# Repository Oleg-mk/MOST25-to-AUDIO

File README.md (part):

# MOST25 to AUDIO

A passive listener for the MOST25 optical ring in a car. It sits in the
fibre as an invisible repeater - physically present, never a node: no
address, never a word on the control channel - and turns what the ring
carries into audio and data the owner can use:

- **J3: what the factory amplifier would play**, as stereo I2S and, the
  same stream, as S/PDIF on TOSLINK and coax: the main source with the head
  unit's volume, mute, balance, bass, treble and loudness applied, and up to
  three more of the amplifier's sinks - navigation and phone, the parking
  sensors, the chimes, where the car sends them as audio - mixed in at their
  own levels, so speakers moved to an
  amplifier or DSP of the owner's choice keep the car's controls and its
  voices;
- **J2: everything, raw**: every frame byte on two TDM8 lines, the control
  channel's blocks on UART, MCLK from the ring - for an analyser or a DSP.
  J2 and J3 show the frame as it leaves the listener: when the phone plays
  into the car's AUX channels, they carry the phone, as the factory
  amplifier after the listener does;
- **phone audio into the car**: a phone's Bluetooth stream while it plays,
  otherwise whatever plays into the board's TOSLINK input, replaces the bytes
  of the car's own AUX source while the amplifier plays them, so it is heard
  through the factory system with the factory controls.

**Status, 2026-10-12: designed and verified in simulation, host tests and
builds, but never built and never tried in a car.** Every file needed to
order, flash and assemble one is in this repository.

**This is a research project.** Every finding, recording, correction or bit
of help is welcome: open an issue or a pull request, or write in the forum
thread.

Its offspring, [JLR-MOST-Reader](https://github.com/Oleg-mk/JLR-MOST-Reader),
is the same receiver, DSP engine, S/PDIF coder and optical front end cut down
to one job on Jaguar and Land Rover: the amplifier's stereo out on TOSLINK.

Ukrainian: [README.uk.md](README.uk.md).

## Which cars

- **What the car must have:** a MOST25 ring that carries the entertainment
  audio to a separate amplifier as plain PCM. Cars without that external
  amplifier keep the audio inside the head unit, and the ring carries little
  or none of it; a copy-protected stream (DTCP) gives nothing to play either.
  Having MOST25 does not make a car one of them - only a recording of that
  car says.
- **Both ring rates:** 48 kHz (Jaguar and Land Rover) and 44.1 kHz (Audi MMI
  2G/3G/3G+, BMW E65/F01). The receiver learns the bit time from the line, and
  the regenerator's clock is centred on the measured rate.
- **The controls:** every source agrees that the PCM on the ring is the same at
  any volume, and that the amplifier applies the volume, balance, tone and
  mixer levels. So the listener reads the control channel and applies them
  itself. Known: Jaguar and Land Rover (the gateway's 0xF0.0x409 levels and the
  amplifier's 0x22.0x46D SpeakerLevel) and BMW (AudioMaster 0x20.0x200);
  Mercedes, VAG and Volvo are not public. Every scale is a placeholder until
  that car's ring is recorded, and the listener's own console trace is the
  tool for it (`listener_fw/README.md`, Recording). Until it has heard one of
  the volume messages it knows, J3 stays silent (the chimes excepted).
- **The phone into the car** needs the car's AUX to be a MOST source: where AUX
  is mixed inside the head unit there are no AUX bytes to replace. It also needs
  the listener on the fibre into the amplifier: the phone goes into the frames
  as they leave the listener, so only the nodes after it hear it. For listening,
  any place in the ring will do.

[docs/vehicle_survey.md](docs/vehicle_survey.md) lists each car with its
sources and how sure each fact is.

## Is it safe for the car's ring?

- **The ring's path:** the fibre receiver, a buffer, a multiplexer (U2) and the
  fibre transmitter. U2 passes either the fibre's own signal or the FPGA's
  regenerated one. That path runs on the always-on 3.3 V (3V3_AON, U5), fed
  from KL30 and drawing tens of microamps with the car parked.
- **The bypass:** U2 falls back to the fibre's own signal whenever the FPGA is
  off or not configured, has not locked to the ring, or its transmit edges
  stop; a watchdog (U11) does that last even if the FPGA's clocks die. So a
  failure of the FPGA, its clocks or the regeneration leaves the ring passing
  straight through.
- **The switch:** when the listener locks and moves the ring from the plain
  path to its regenerated one, the ring sees a short phase step, as it does when
  any MOST node leaves its bypass at start-up. The next node relocks within a few
  frames, and the amplifier may mute for that moment.
- **When the ring opens:** the bypass is an electrical path, not an optical
  one. If its supply is lost (a blown fuse, KL30 disconnected) or a fibre part
  fails, the ring opens, as with every factory MOST node. Fit your own fuse
  where you tap KL30.
- **Nothing new on the network:** no address, never a word on the control
  channel. Until injection is allowed, the frames leave as they came.
- **Injection is off until you allow it** ('i' on the host's console, kept in
  flash; a new module has it off). Then it replaces only the bytes of the car's
  own AUX source while the amplifier plays them, and the FPGA drops it 2 s after
  the host's last command, so a host that hangs takes the phone out.
- **Fully reversible:** unplug the loop-in cable and the car is back to stock.

## Status: what is proved and what is not

**Verified in models** (run `python check_all.py`; every step passes, and
`--sweep` adds 32 random rings):

- The gateware, in Icarus Verilog against Python models:
  - the receiver, and the J3 engine at 48 and 44.1 kHz, word for word against
    its model;
  - the S/PDIF output, decoded back;
  - the whole core from the optical line, in 14 corners: both rates, preamble
    variants, injection, gaps in the control blocks, a dead transmit feedback, a
    stopped clock, bit errors, the Si514's start and its loss, the capture,
    fades, the injection's lease, and a deliberate fault the checks must catch;
  - the regenerator's clock loop, and 32 random rings.
- The host's firmware: its tests on the PC and the ESP-IDF build with no
  warnings. JLR-MOST-Reader's checks compile its decoder and gain tables and
  compare them with their own.
- The Gowin build meets timing with at least 10 % margin; the bitstream and
  the firmware in `kit/2_flash` were built from the committed sources.
- The boards: ERC and DRC clean, with parity between sheet and board, for v1.6
  and v2.0; v2.0's sheet held to v1.6's part for part and net for net; the
  board's fit in the tube and its caps from one model; the fab packages and
  the kit reproduced from the commit.
- The laptop's recorder and decoder, against the host's own formats.

**Unknown until a bench or a car:**

- **The line:** the preamble's full pattern, which variant marks a block start,
  the parity rule. The simulations assume them; the capture (command 04)
  settles them on the first ring.
- **The per-car scales:** volume, tone and the mixer levels stay placeholders
  until a recording of the car's controls.
- **The car's own messages:** whether a stock head unit sends 0x22.0x111
  Connect at all (J3 and the phone into the car take their channels from it);
  which of 0xF0.0x409 and SpeakerLevel a Jaguar XF's amplifier gets, and
  0x409's byte positions (two layouts in one author's code, the later one
  used); whether JLR mutes with 0x113 or with 0x466 MuteParameters; whether
  the parking sensors and the chimes travel the ring as audio, as mObridge's
  guide says for JLR. The capture and the recording settle these too.
- **Real hardware:** no board has been powered, the regeneration has never run
  in a real ring, and no real S/PDIF receiver has taken the output.

Bring-up goes in three steps, each with a recording (Bring-up, in this order,
below).

## Build one

The full guide is [BUILD.md](BUILD.md); `kit/` holds the same in Ukrainian with
every file to order, flash and fit. There are two boards with the same
circuit. **v2.0** (`listener_hw2/`) is the one to build: 98 x 60 mm, four
layers, inside an 80 x 30 x 2 mm aluminium tube with two 3D-printed end caps.
v1.6 (`listener_hw/`) is the first, flat board, 123.55 x 78.9 mm on two layers.

1. **Order the boards** from JLCPCB, with the SMD parts assembled on both
   sides. Everything is in `listener_hw2/fab/`, copied into `kit/1_boards/`.
   One board gives three assemblies:

   | Assembly | What works | Parts JLCPCB places |
   |---|---|---|
   | min | the core and the S/PDIF outputs: J6 (TOSLINK) and J7 (coax) | 103 |
   | mid | min and the line out, J8 and J9 | 143 |
   | max | mid and the TOSLINK input, J5 | 163 |

   U7, the Si514, is not in JLCPCB's stock: send your own, or have JLCPCB pre-order it.
   Any 3.3 V CMOS variant in the 3.2 x 5 or 2.5 x 3.2 package fits, for example
   514CBB000112BAG, which DigiKey sells singly and JLCPCB can pre-order (C1670489).
2. **Buy the hand-soldered parts:** J1 (TE 1-1394640-1, the MOST FOT header:
   marketplaces only, look early), J4 (Molex 43650-0200), J5 and J6 (Cliff
   FCR684208R and FCR684208T), J7..J9 (BKL Electronic 0101153), J2 and J3 (pin
   headers), M1 (Sipeed Tang Nano 20K), M2 (Espressif ESP32-DevKitC-VIE) and the
   modules' pin headers.
3. **The enclosure:** the tube, cut to the soldered board's length; the two
   caps, printed from `listener_hw2/caps/` in PETG or ASA; a 150 mm U.FL-to-SMA
   pigtail and a 2.4 GHz antenna; screws.
4. **Flash both modules before soldering them** (`kit/2_flash/`): once M1 is in,
   the RCA jacks cover its USB-C.
5. **Assemble, power up on the bench, then fit the tube**, as BUILD.md says.
6. **In the car**, one step at a time, each with a recording (`kit/3_laptop/`):
   the bypass and listening first, then the regeneration, then the injection.

Also needed: a 12 V feed from KL30 with a fuse of your own, and a loop-in cable
that opens the ring at one node and brings it to J1 (Kufatec, Dension and
Trioma make them).

## Rough cost

| Item | Approx. USD | Basis (seen 2026-10-12) |
|---|---|---|
| JLCPCB: 5 boards, 2 of them assembled on both sides | min 200-230, mid 225-255, max 275-310, plus shipping and tax | JLCPCB's quote and assembly price page: 5 bare boards (4 layers, ENIG) $25; SMD on both sides needs Standard PCBA, $51 setup and $16 stencil for both sides plus $1.53 per part line; the parts for two boards $25 (min) to $75 (max), most of max's being U13 (SRC4192, about $17.56); two Si514s pre-ordered, $17-24 |
| Sipeed Tang Nano 20K | 26-32 | $25 at launch; Spotpear $31.90 |
| Espressif ESP32-DevKitC-VIE | 11-14 | DigiKey $11.00 |
| TE 1-1394640-1 (J1) | 22-27, plus shipping | no distributor stocks it; eBay about $22 (2026-10-12), AliExpress about $27 (2026-10-13) |
| Cliff FCR684208R and FCR684208T (J5, J6) | 13 | DigiKey $7.83 + $5.22 |
| 3 x BKL Electronic 0101153 (J7..J9) | 28-33 | Bürklin, €8.35-9.94 each |
| J4 with its plug, the pin headers, a fuse and wire for the 12 V tap | 5-10 | DigiKey; the fuse and wire rough |
| The tube, the printed caps, screws | 3-12 | the tube about 335 UAH a metre; 23 g of PETG |
| U.FL-to-SMA pigtail and a 2.4 GHz antenna | 4-11 | Adafruit 851 $3.95; a TE Linx antenna $7.13 |
| MOST loop-in adapter, TOSLINK cable | 25-50, plus shipping | a MOST25 splitter on Tindie $20, a Dension set about €40, depending on the node you tap; TOSLINK $5-7 |

The first listener comes to roughly $340-435 for min, $365-460 for mid and $415-515 for max,
plus shipping and tax. The second board from the same order is already assembled and paid for:
its modules, hand parts, enclosure and cables add about $140-205. Most of the order is JLCPCB's
fixed fees for assembling both sides, so more boards from one order cost less each.

## Repository map

| Folder | What | Built with |
|---|---|---|
| [listener_hw2](listener_hw2) | **board v2.0, the one to order**: v1.6's circuit on 98 x 60 mm and four layers, for an aluminium tube 80 x 30 x 2 mm; the sheet written by `gen_listener2.py` from v1.6's generator and held to v1.6 by `tools/check_v2_circuit.py`; the manufacturing package for three assemblies in `fab/`, written by `make_fab2.py`; the board in the tube modelled by `check_fit.py`, the two printed end caps in `caps/`, written by `gen_caps.py`; the pictures in `views/`, rendered by `make_views.py` - see The board, v2.0 | Python, KiCad 10 |
| [listener_hw](listener_hw) | board v1.6, the first one, and the circuit's source: one KiCad 10 sheet, generated by `gen_listener.py` (symbols and the footprints drawn from the makers' drawings included: Si514, the TOSLINK housings, the RCA jack, both modules; the bodies of the FOT, the TOSLINK housings and the RCA jack for the 3D view too); the manufacturing package in `fab/`, written by `make_fab.py`: Gerbers and drill files, BOM, pick-and-place, and JLCPCB's BOM and CPL for an order with the SMD parts assembled; TOSLINK in through DIR9001 and SRC4192, S/PDIF out on TOSLINK and coax; J3's stereo as an analog line out on two RCA through a PCM5102A and an OPA1678 buffer with a 60 kHz low-pass; test points for the bench. The PCB, 123.55 x 78.9 mm on two layers, first laid out by `gen_listener_pcb.py` from the same sheet (every part's place and why is in that file), placed by hand in KiCad and routed over a ground plane - see Board v1.6 | Python, KiCad 10 |
| [listener_gw](listener_gw) | FPGA (Sipeed Tang Nano 20K): receiver, regenerator on a ring-locked clock (an Si514 the FPGA steers), TDM/UART outputs, J3's DSP engine and its S/PDIF twin, audio injection from the host or the S/PDIF input | Gowin EDA 1.9.12; simulation: Icarus Verilog (OSS CAD Suite) |
| [listener_fw](listener_fw) | ESP32 host (M2, ESP32-DevKitC-VIE): Bluetooth A2DP in (AAC, SBC), the phone's rate onto the ring's, MOST telegram decoding, the amplifier model, J3's coefficients, the steering wheel's track keys to the phone (AVRCP) | ESP-IDF v6.1; host tests: gcc |
| [virtual_most_source](virtual_most_source) | MOST25 frames and Biphase Mark line coding - the simulations' stimulus | Python + numpy |
| [tools](tools) | `console_log.py`: a recording of the host's console on a laptop on M2's USB port, kept whole, with marks and alarms (the port lost, the ESP32 started anew, a loss counter rising, silence); `trace_decode.py`: that recording at home - every telegram, the sound values a car's scales are fixed from, the telegrams beside each mark, the starts, losses and silences, and each dump through `capture_analyse.py`: what a recording of a real line says (UI and rate, preamble patterns, block marker, parity rule, frame control); each with its test (the console's formats against host.c's own, a made-up recording, known frames) | Python; pyserial for the recorder |
| [kit](kit) | what the project hands over, without the rest of the repository: `1_boards` v2.0's order (JLCPCB's files for the three assemblies, the BOM, the schematic and assembly PDFs, the parts by hand, the tube's printed caps, the first power-up, the assembly into the tube), `2_flash` the FPGA's bitstream and the host's firmware with how to write each from Windows or macOS, `3_laptop` the recorder and the decoder with their launchers; written by `tools/make_kit.py`, the builds only from committed sources, checked by `check_all.py` | Ukrainian READMEs; the same in English is [BUILD.md](BUILD.md) |
| [BUILD.md](BUILD.md) | the build guide in English: the order, the parts, flashing, the assembly, the tube, the first power-up, the laptop's recorder | - |
| [SOURCES.md](SOURCES.md) | where the knowledge of MOST25, of the cars' messages and of the parts comes from | - |
| [docs](docs) | the MOST control formats the host decodes, which cars carry audio and how they send volume, the research behind the regenerator's clock | - |

Each part's README says how it works, what is verified and how.

## Build and test

```text
python check_all.py            everything, one step at a time (~40 min)
python check_all.py --quick    without the clock loop's long runs
python check_all.py --sweep    plus the whole core over 32 random rings (~1 h more)
```

It runs the steps strictly one after another and stops at nothing: each
prints PASS or FAIL, and the summary lists them. The simulation scripts
themselves run one simulation at a time too. Tools it expects (override with
environment variables, see the script's header):
OSS CAD Suite in `~/toolchains/oss-cad-suite`, Gowin EDA in
`C:\Gowin\Gowin_V1.9.12.03_x64`, ESP-IDF v6.1 in `~/toolchains/esp-idf`
(tools in `~/toolchains/espressif`), MinGW gcc in `~/toolchains/mingw64`,
KiCad 10.

## The board, v2.0

v2.0 (`listener_hw2/`; `most_listener_v2.kicad_pro` opens it in KiCad 10) is the board to order:
v1.6's circuit on a board of 98 x 60 mm with four layers, made to slide into an aluminium tube
80 x 30 x 2 mm closed by two printed caps. The inputs sit at one end - J1 (the ring's FOT), J5
(TOSLINK in), J4 (power) - and the outputs at the other - J6 (TOSLINK out), J7 (coax S/PDIF), J8
and J9 (the line out). M1 (the FPGA) stands on top; M2 (the host) hangs underneath, component side
down, its micro-USB at the input end. In1 and In2 are solid ground under both signal layers.

- **The sheet** is not drawn twice. `gen_listener2.py` loads v1.6's `gen_listener.py` and writes its
  blocks with v2.0's title and UUIDs, J5 and J6 as Cliff ORJ-8/OTJ-8 (10 mm high, no screw ear), the
  modules' footprints with holes only for the pins in use and the corner pins, and the parts
  v2.0 adds: R47 10R + C84 10u and R48 10R + C85 10u filter the line out's rails,
  R49..R51 (33R) sit in I2S's BCLK, LRCK and DOUT, R52 (33R) in RX_IN at U3, R53 (33R) at U1's
  output. `tools/check_v2_circuit.py` holds the sheet to v1.6's part for part and net for net, these
  parts taken out, so the gateware, the firmware and `kit/2_flash` hold for both boards.
- **The PCB** was placed once by `gen_listener2_pcb.py` and routed, then edited round by round in
  the PCB editor; the ring's FOT block is the reader v2.0's (JLR-MOST-Reader). It passes DRC with no
  error, nothing unconnected and no difference from the sheet.
- **Three assemblies, one board and one case.** Every connector is fitted in each; they differ in
  the parts behind the connectors: min (the core and the S/PDIF outputs), mid (+ the line out), max
  (+ the TOSLINK input). `make_fab2.py` writes `fab/` from the board and the sheet: the Gerbers and
  drill files, the BOM, the pick-and-place of both sides, JLCPCB's BOM and CPL for each assembly,
  the schematic and the assembly drawings of both sides, and a README with the order's steps.
- **The tube.** `check_fit.py` models the board in the tube from the PCB and every part's height,
  each with its source: the board centred across, 8 mm a side, at the height that leaves the same
  room over the tallest parts on top (the RCA jacks) and under M2; each part's face against its cap;
  the leads under the board; the caps' openings and the webs between them. `gen_caps.py` writes the
  caps into `caps/` (STEP, STL, a drawing, a README), and writes nothing when a wall comes out
  thinner than a printer makes or a block meets a part or a lead. Each cap is a flange on the tube's
  end, blocks in the side margins that hold the board's edges in slots, 0.7 mm off the tube's walls
  so any tube in tolerance takes them, and a saddle under the tube with an ear either side to screw
  it down. The input cap passes J1, J5 with J4, M2's micro-USB and the Bluetooth antenna's SMA jack;
  the output cap J6 and the RCA jacks.
- **What the tube asks.** M1's USB-C ends up behind the RCA housings, so the FPGA is flashed before
  M1 is soldered in and cannot be flashed in the assembled board; the host's micro-USB stays
  reachable through the input cap, for its firmware and for the laptop's recording. J2 and J3 are
  for the bench: a crimp housing on them would stand 16.4 mm high, and the tube leaves 14.75.
- **The pictures** here are rendered by `make_views.py` from the same models. KiCad has no body for
  the modules and four of the parts, and plain boxes stand in for them.

`check_all.py` regenerates v2.0's sheet and holds it to v1.6's, runs ERC and DRC, runs
`check_fit.py` and `gen_caps.py`, and fails while `fab/` or `caps/` differ from what their scripts
write. `kit/1_boards` hands v2.0 over: the order of each assembly, the parts by hand, the tube and
its caps, the assembly into the tube.

## Board v1.6

Board v1.6 is the first board, on two layers; its sheet is v2.0's circuit too.
`listener_hw/most_listener.kicad_pro` opens the project in KiCad 10. The sheet
is generated (`gen_listener.py`); the PCB was laid out once by
`gen_listener_pcb.py`, then placed by hand in the PCB editor and routed. From there on
`most_listener.kicad_pcb` is the master: parts may be moved freely, and the
generator refuses to overwrite the file unless run with `--fresh`, which lays
the parts out again from its table and discards every track.

What the board already carries: the outline (123.55 x 78.9 mm, two layers), four
M3 holes about 4 mm from their edges, ground pours on both sides (B fills them), the copper keep-out
under M2's antenna, the net classes - Default 0.25 mm tracks with 0.15 mm
clearance, Rail 0.35 mm for the 3.3 V rails, Power 0.6 mm for the battery path
and the 5 V rails, vias 0.6/0.3 and 0.8/0.4 mm - and `most_listener.kicad_dru`,
which lets one resolved thermal spoke connect a pad to a pour. The reasons
behind every part's place are in the generator's table.

The routing (board v1.6): the bottom is one ground plane, crossed only by
short jumpers (4 of them, 9 mm in all, the longest 3.65 mm); signals and
supplies run on top, the supplies as wide tracks that change layer nowhere but
at one 3V3_AON jumper, and the top's ground pour is stitched to the plane by
vias about every 6 mm. Every SMD ground pad has a via of its own beside it. The
5 V trunk runs 1 mm wide from C7 up the left edge under J1 and along the top
edge; the host's switch U10 sits at M2's 5 V pin with 10 uF at its input (the
radio's pulses come out of it, not over the trunk); 100 uF + 100 nF (C63, C64)
sit by D3 at the module's end of the trunk, 100 uF + 100 nF (C81, C80) at its
other end by U10 and U14, four more 100 nF (C65-C68) along it.
M1 and M2 are soldered to the board on pin headers, no sockets - two 1x20 and
two 1x19 on 2.54 mm, which the 3D view shows under them, as it shows J2's and
J3's. The headers' plastic leaves 2.5 mm under each module: room for the 0603
resistors under M1 (R11, R12) and under M2 (R18..R21, R34..R41);
M2's courtyard is its two pin rows and the antenna's end.
KiCad has no model for the MOST FOT, the TOSLINK housings or the RCA jacks, so
`gen_listener.py` draws their bodies from the same drawings, as STEP files in
`most_listener.3dshapes`.
`make_fab.py` writes the manufacturing package into `listener_hw/fab`: the
Gerbers and drill files (zipped for the board house), the BOM, the pick-and-place
file, the same two in JLCPCB's format, and a README with the board's numbers and
the notes the BOM's values do not carry. JLCPCB's rotations were read off each
chosen part's LCSC footprint.
`check_all.py` fails while the package does not match the board.

Every footprint is linked to its symbol, so after a change of the sheet: run
`gen_listener.py`, then in the PCB editor Tools > Update PCB from Schematic. `python check_all.py` runs KiCad's DRC on
the board as it is, checked against the sheet; the board passes with no error
and nothing unconnected. Warnings are silk only: references the hand placement
left overlapping a pad or another reference.

## Limits, by design

- **Only the light tells the host what plays.** The listener never sends a
  word, so the host learns which frame bytes carry the AUX source, and whether
  the amplifier plays them, only from the telegrams it happens to hear. At a
  cold start the ring, the FPGA and the ESP32 wake together (WAKE); if the
  head unit connects the amplifier to AUX before the host is listening, the
  phone is not injected until the head unit next changes a source. The FPGA
  reads its bitstream from the module's flash in about 290 ms, so that window
  is kept short. Asking (a SourceInfo.Get on the control channel) would end
  the listener's silence, so this stays as it is.
- **Cars whose AUX is not a MOST source** - mixed inside the head unit - have
  no AUX bytes to replace; the phone cannot be injected there. Listening
  (J2, J3) needs the audio on the fibre as plain PCM: cars without the
  external amplifier, or with a copy-protected stream (DTCP), give it nothing
  to play (docs/vehicle_survey.md). Having MOST25 does not make a car one of
  them - only a recording of that car says.
- **The per-car scales** - volume, tone, the Jaguar XF's navigation and
  parking-sensor levels (0xF0.0x409 bytes 9 and 11) - are placeholders until
  a real ring is recorded.
- **Sink 4 is the chimes in every car**, as Jaguar Land Rover numbers the
  amplifier's sinks: with no SpeakerLevel of its own it plays at -6 dB,
  never at the volume, so a chime is heard with the volume down. A car
  that puts something else on sink 4 gets that at -6 dB too.
- **What an amplifier does on its own** is not on the bus: if it turns the
  music down while a prompt plays, J3 does not; it follows what the head unit
  sends (levels, mutes).
- **The control channel's CRC is not checked**: its polynomial is in no
  document we have. What is checked instead: the FPGA drops a block in which
  the line broke its code, and the host drops a block whose frames disagree
  in parity (the count a clean block has is learnt on the ring). A bit can
  still flip unseen in a way neither shows; the CRC follows once a recording
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
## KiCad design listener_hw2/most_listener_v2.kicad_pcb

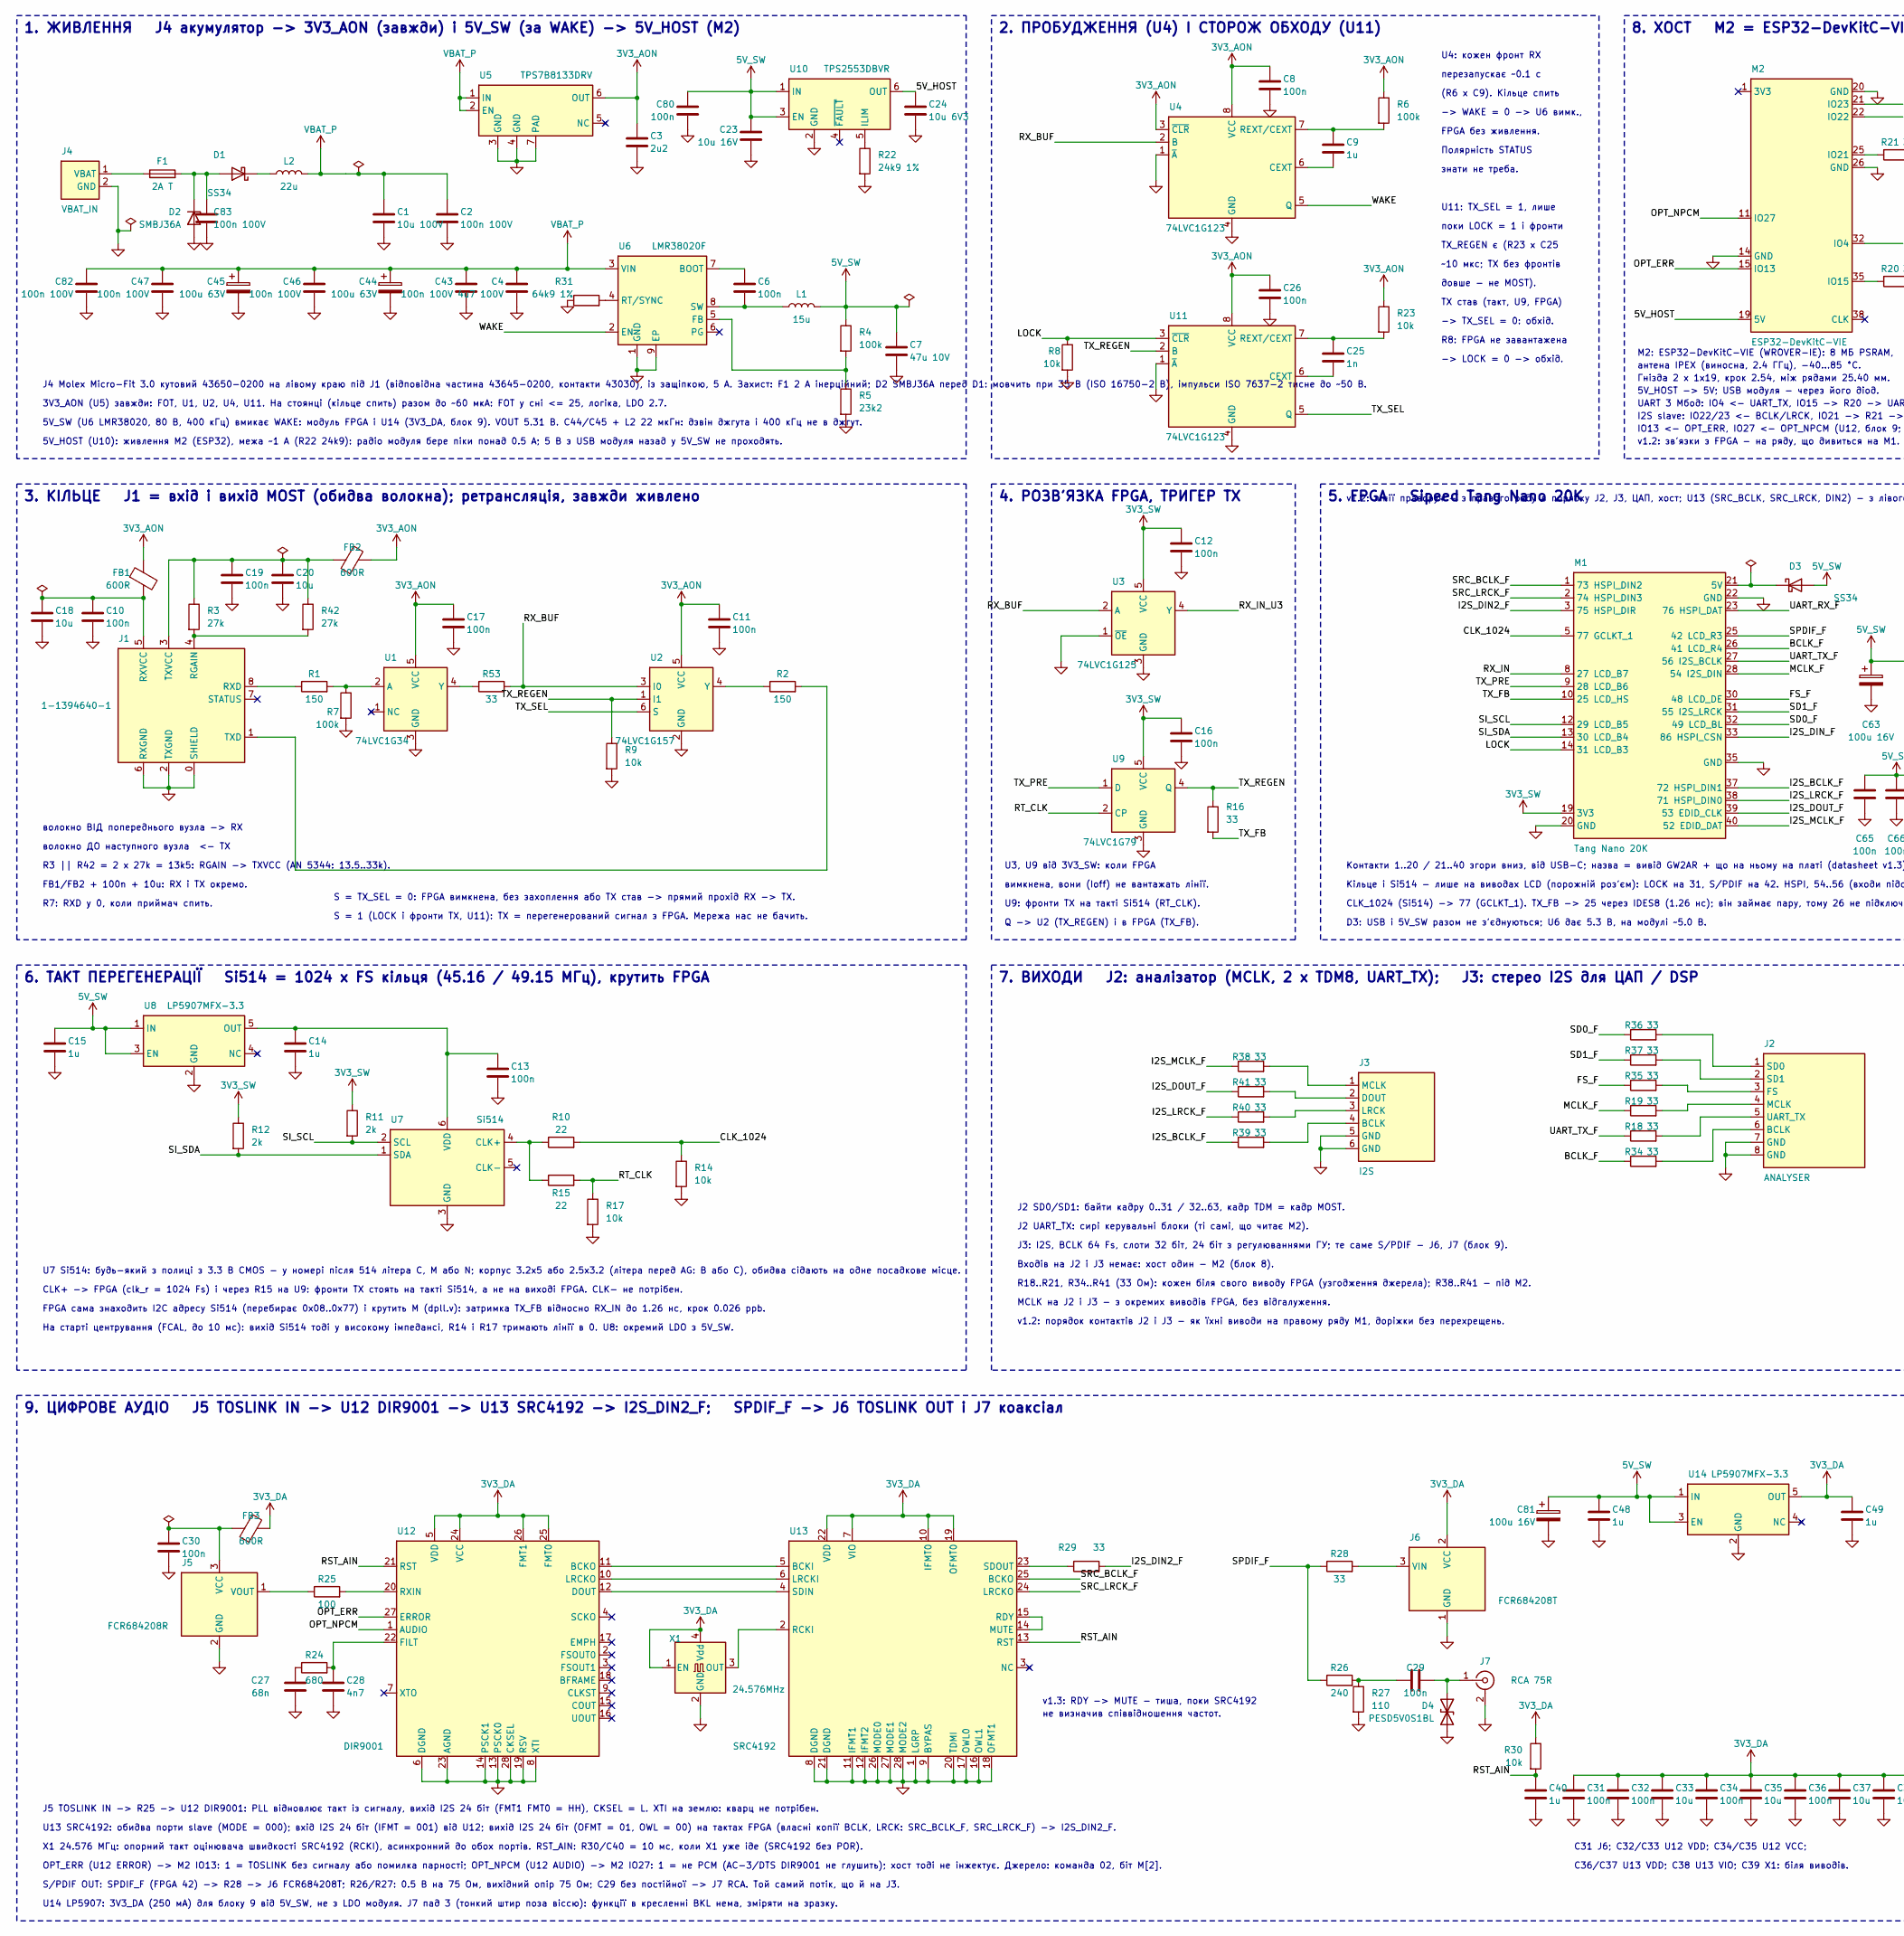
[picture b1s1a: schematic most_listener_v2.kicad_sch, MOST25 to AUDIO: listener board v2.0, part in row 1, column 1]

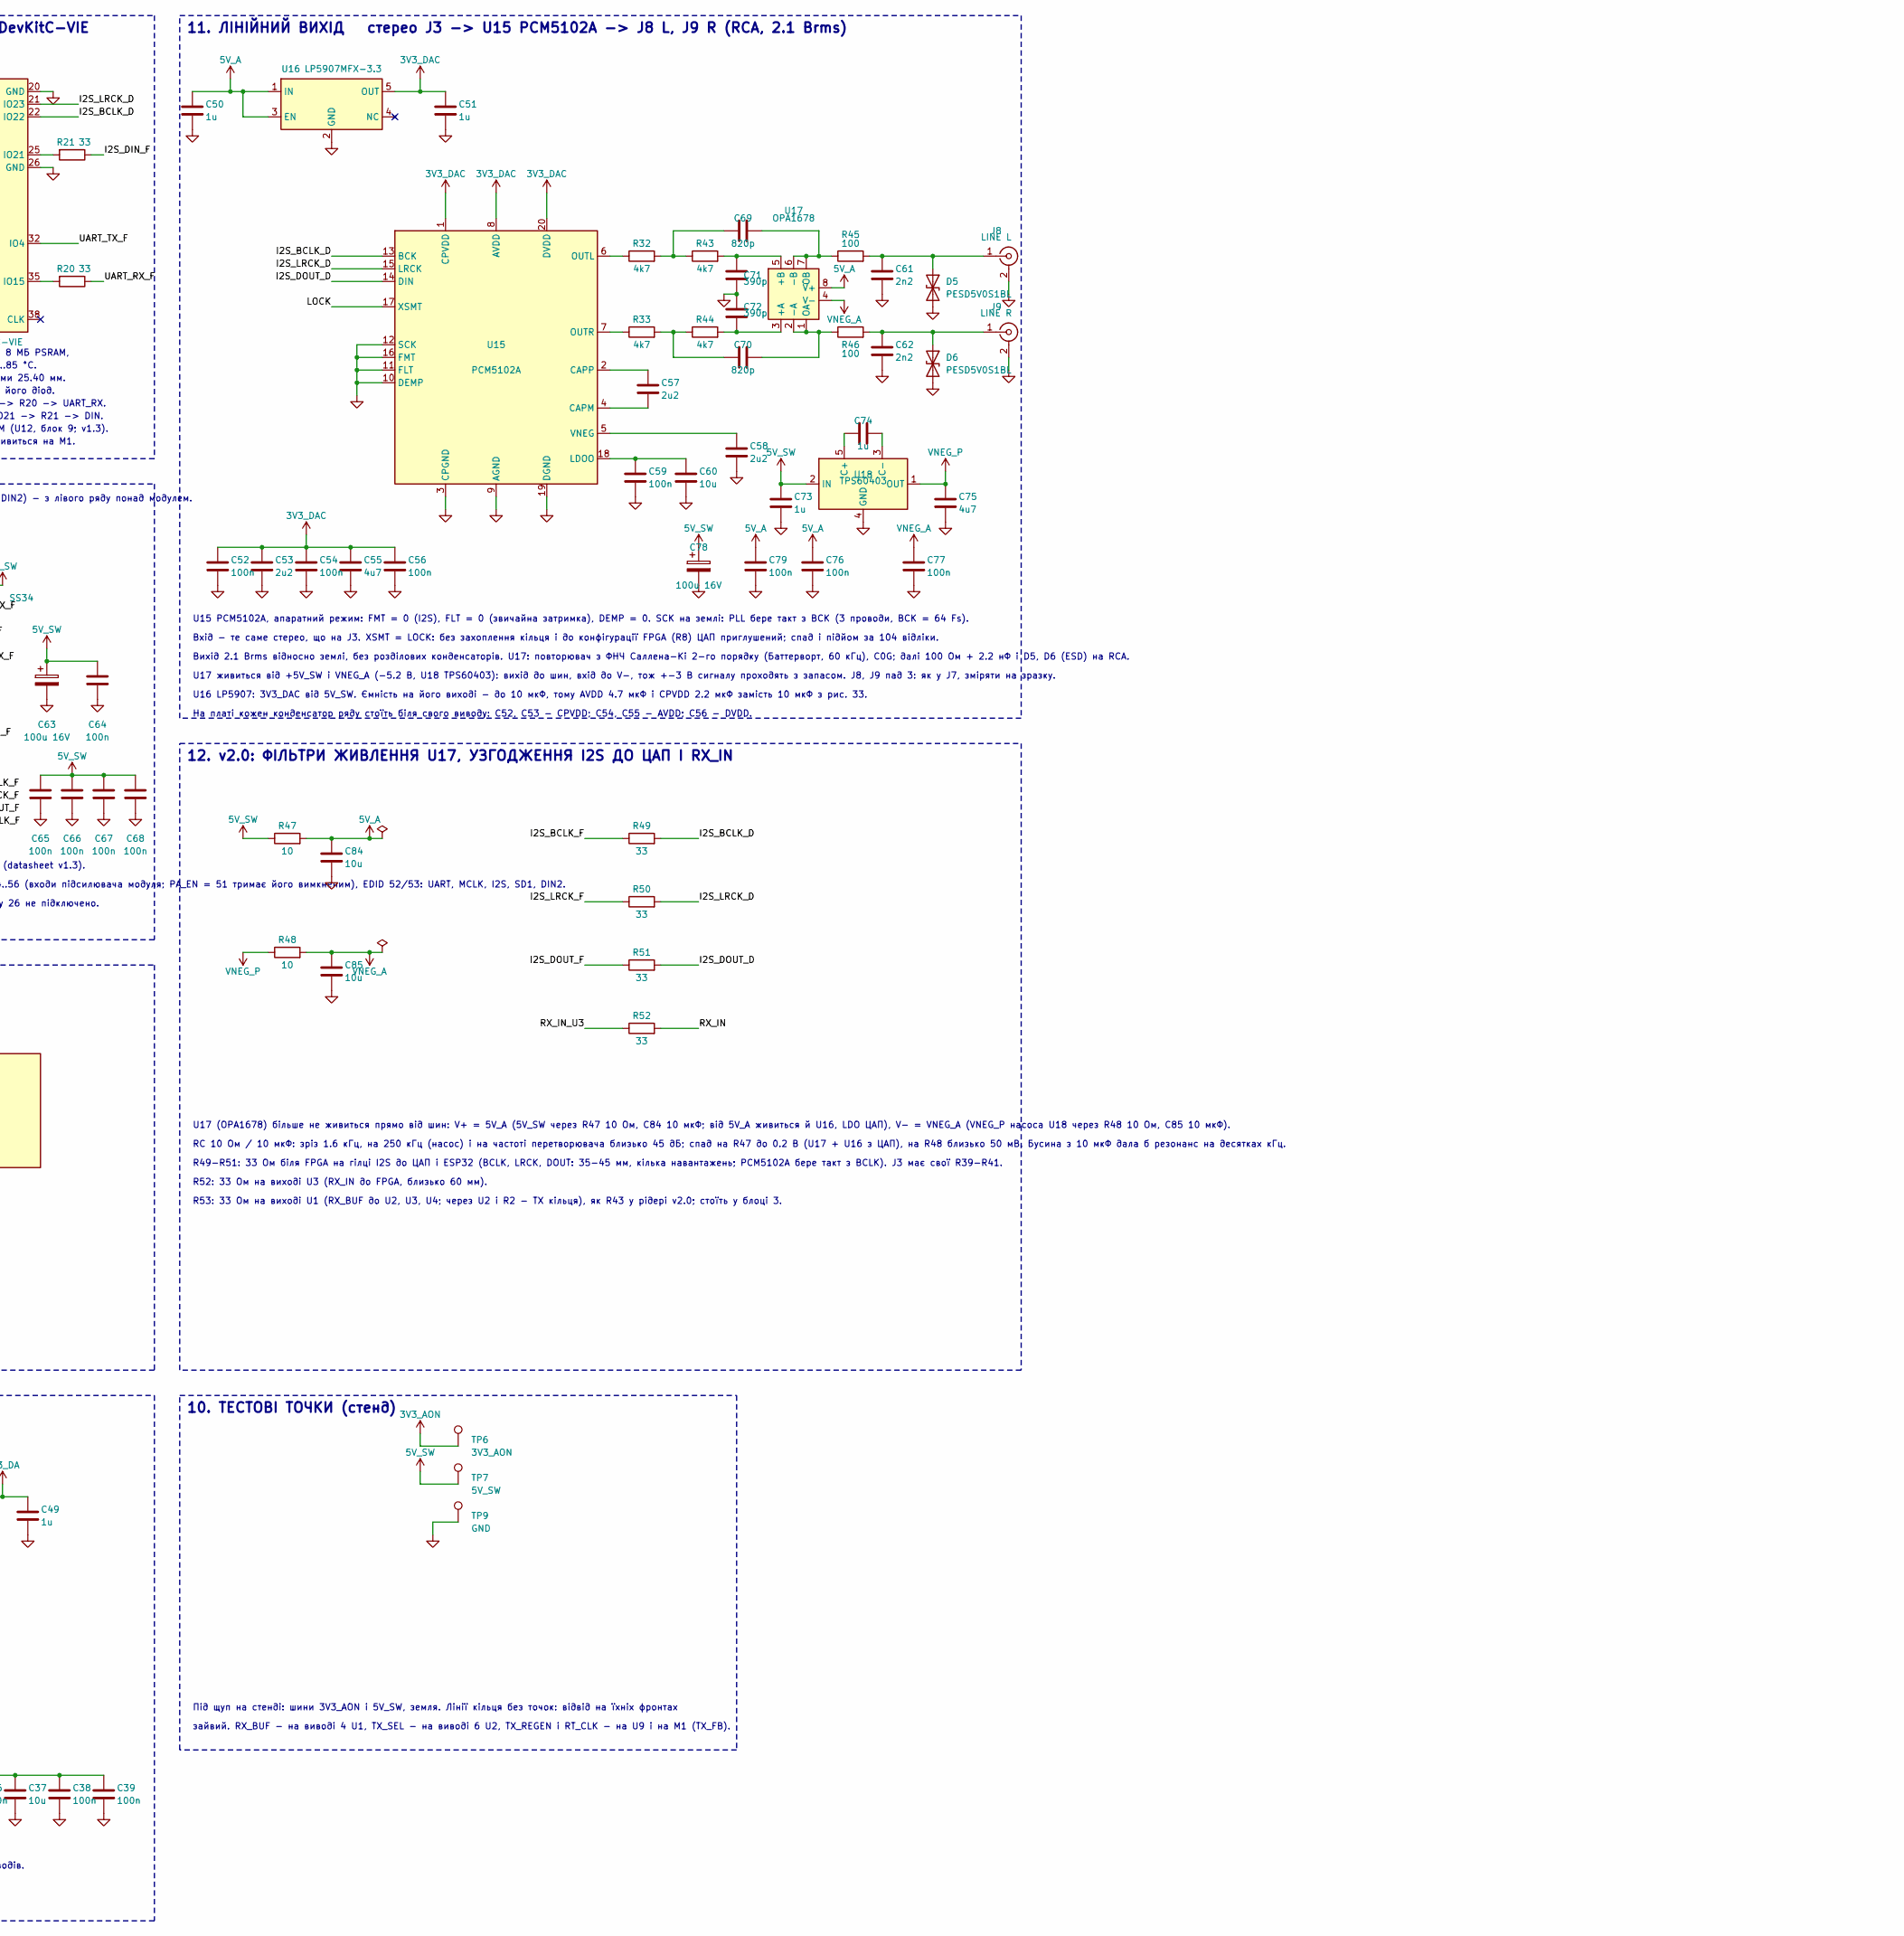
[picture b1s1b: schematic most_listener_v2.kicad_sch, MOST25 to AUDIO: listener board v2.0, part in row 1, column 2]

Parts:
C1: 10u 100V; C_1210_3225Metric
C2, C43, C46, C47, C82, C83: 100n 100V; C_0603_1608Metric
C3, C53, C57, C58: 2u2; C_0603_1608Metric
C4: 4u7 100V; C_1210_3225Metric
C6, C8, C10, C11, C12, C13, C16, C17, C19, C26, C29, C30, C31, C32, C34, C36, C38, C39, C52, C54, C56, C59, C64, C65, C66, C67, C68, C76, C77, C79, C80: 100n; C_0603_1608Metric
C7: 47u 10V; C_1210_3225Metric
C9, C14, C15, C40, C48, C49, C50, C51, C73, C74: 1u; C_0603_1608Metric
C18, C20, C33, C35, C37, C60, C84, C85: 10u; C_0805_2012Metric
C23: 10u 16V; C_0805_2012Metric
C24: 10u 6V3; C_0805_2012Metric
C25: 1n; C_0603_1608Metric
C27: 68n; C_0603_1608Metric
C28: 4n7; C_0603_1608Metric
C44, C45: 100u 63V; CP_Elec_10x10.5
C55, C75: 4u7; C_0805_2012Metric
C61, C62: 2n2; C_0603_1608Metric
C63, C78, C81: 100u 16V; CP_Elec_6.3x7.7
C69, C70: 820p; C_0603_1608Metric
C71, C72: 390p; C_0603_1608Metric
D1, D3: SS34; D_SMA
D2: SMBJ36A; D_SMB
D4, D5, D6: PESD5V0S1BL; D_SOD-882
F1: 2A T; Fuse_1206_3216Metric
FB1, FB2, FB3: 600R; L_0603_1608Metric
J1: 1-1394640-1; TE_MOST_Pigtail_FOT_2+0
J2: ANALYSER; PinHeader_1x08_P2.54mm_Vertical
J3: I2S; PinHeader_1x06_P2.54mm_Vertical
J4: VBAT_IN; Molex_Micro-Fit_3.0_43650-0200_1x02_P3.00mm_Horizontal
J5: FCR684208R; Cliff_TOSLINK_ORJ8_OTJ8
J6: FCR684208T; Cliff_TOSLINK_ORJ8_OTJ8
J7: RCA 75R; BKL_0101153_RCA_RA
J8: LINE L; BKL_0101153_RCA_RA
J9: LINE R; BKL_0101153_RCA_RA
L1: 15u; L_Bourns_SRN6045TA
L2: 22u; L_Bourns-SRN8040_8x8.15mm
M1: Tang Nano 20K; Sipeed_TangNano20K
M2: ESP32-DevKitC-VIE; Espressif_ESP32-DevKitC_V4
R1, R2: 150; R_0603_1608Metric
R3, R42: 27k; R_0603_1608Metric
R4, R6, R7: 100k; R_0603_1608Metric
R5: 23k2; R_0603_1608Metric
R8, R9, R14, R17, R23, R30: 10k; R_0603_1608Metric
R10, R15: 22; R_0603_1608Metric
R11, R12: 2k; R_0603_1608Metric
R16, R18, R19, R20, R21, R28, R29, R34, R35, R36, R37, R38, R39, R40, R41, R49, R50, R51, R52, R53: 33; R_0603_1608Metric
R22: 24k9 1%; R_0603_1608Metric
R24: 680; R_0603_1608Metric
R25, R45, R46: 100; R_0603_1608Metric
R26: 240; R_0603_1608Metric
R27: 110; R_0603_1608Metric
R31: 64k9 1%; R_0603_1608Metric
R32, R33, R43, R44: 4k7; R_0603_1608Metric
R47, R48: 10; R_0603_1608Metric
TP6: 3V3_AON; TestPoint_Pad_D2.0mm
TP7: 5V_SW; TestPoint_Pad_D2.0mm
TP9: GND; TestPoint_Pad_D2.0mm
U1: 74LVC1G34; SOT-353_SC-70-5
U2: 74LVC1G157; SOT-363_SC-70-6
U3: 74LVC1G125; SOT-353_SC-70-5
U4, U11: 74LVC1G123; VSSOP-8_2.3x2mm_P0.5mm
U5: TPS7B8133DRV; WSON-6-1EP_2x2mm_P0.65mm_EP1x1.6mm
U6: LMR38020F; Texas_HSOP-8-1EP_3.9x4.9mm_P1.27mm_ThermalVias
U7: Si514; Si514_3.2x5_2.5x3.2
U8, U14, U16: LP5907MFX-3.3; SOT-23-5
U9: 74LVC1G79; SOT-353_SC-70-5
U10: TPS2553DBVR; SOT-23-6
U12: DIR9001; TSSOP-28_4.4x9.7mm_P0.65mm
U13: SRC4192; SSOP-28_5.3x10.2mm_P0.65mm
U15: PCM5102A; TSSOP-20_4.4x6.5mm_P0.65mm
U17: OPA1678; SOIC-8_3.9x4.9mm_P1.27mm
U18: TPS60403; SOT-23-5
X1: 24.576MHz; Oscillator_SMD_Abracon_ASE-4Pin_3.2x2.5mm

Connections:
3V3_AON: C3.1, C8.1, C11.1, C17.1, C26.1, FB1.1, FB2.2, R6.1, R23.1, TP6.1, U1.5 (VCC), U2.5 (VCC), U4.3 (~CLR), U4.8 (VCC), U5.6 (OUT), U11.8 (VCC)
3V3_DA: C31.1, C32.1, C33.1, C34.1, C35.1, C36.1, C37.1, C38.1, C39.1, C49.1, FB3.2, J6.2 (VCC), R30.1, U12.5 (VDD), U12.24 (VCC), U12.25 (FMT0), U12.26 (FMT1), U13.7 (VIO), U13.10 (IFMT0), U13.19 (OFMT0), U13.22 (VDD), U14.5 (OUT), X1.1 (EN), X1.4 (Vdd)
3V3_DAC: C51.1, C52.1, C53.1, C54.1, C55.1, C56.1, U15.1 (CPVDD), U15.8 (AVDD), U15.20 (DVDD), U16.5 (OUT)
3V3_SW: C12.1, C16.1, M1.19 (3V3), R11.1, R12.1, U3.5 (VCC), U9.5 (VCC)
5V_A: C50.1, C76.1, C79.1, C84.1, R47.2, U16.1 (IN), U16.3 (EN), U17.8 (V+)
5V_SW: C7.1, C15.1, C23.1, C48.1, C63.1, C64.1, C65.1, C66.1, C67.1, C68.1, C73.1, C78.1, C80.1, C81.1, D3.2 (A), L1.2, R4.1, R47.1, TP7.1, U8.1 (IN), U8.3 (EN), U10.1 (IN), U10.3 (EN), U14.1 (IN), U14.3 (EN), U18.2 (IN)
/5V_HOST: C24.1, M2.19 (5V), U10.6 (OUT)
/BCLK_F: M1.26 (41 LCD_R4), R34.1
/CLK_1024: M1.5 (77 GCLKT_1), R10.2, R14.1
/FS_F: M1.30 (48 LCD_DE), R35.1
/I2S_BCLK_D: M2.22 (IO22), R49.2, U15.13 (BCK)
/I2S_BCLK_F: M1.37 (72 HSPI_DIN1), R39.1, R49.1
/I2S_DIN2_F: M1.3 (75 HSPI_DIR), R29.2
/I2S_DIN_F: M1.33 (86 HSPI_CSN), R21.1
/I2S_DOUT_D: R51.2, U15.14 (DIN)
/I2S_DOUT_F: M1.39 (53 EDID_CLK), R41.1, R51.1
/I2S_LRCK_D: M2.21 (IO23), R50.2, U15.15 (LRCK)
/I2S_LRCK_F: M1.38 (71 HSPI_DIN0), R40.1, R50.1
/I2S_MCLK_F: M1.40 (52 EDID_DAT), R38.1
/LOCK: M1.14 (31 LCD_B3), R8.1, U11.3 (~CLR), U15.17 (XSMT)
/MCLK_F: M1.28 (54 I2S_DIN), R19.1
/OPT_ERR: M2.15 (IO13), U12.27 (ERROR)
/OPT_NPCM: M2.11 (IO27), U12.1 (AUDIO)
/RST_AIN: C40.1, R30.2, U12.21 (RST), U13.13 (RST)
/RT_CLK: R15.2, R17.1, U9.2 (CP)
/RX_BUF: R53.2, U2.3 (I0), U3.2 (A), U4.2 (B)
/RX_IN: M1.8 (27 LCD_B7), R52.2
/RX_IN_U3: R52.1, U3.4 (Y)
/SD0_F: M1.32 (49 LCD_BL), R36.1
/SD1_F: M1.31 (55 I2S_LRCK), R37.1
/SI_SCL: M1.12 (29 LCD_B5), R11.2, U7.2 (SCL)
/SI_SDA: M1.13 (30 LCD_B4), R12.2, U7.1 (SDA)
/SPDIF_F: M1.25 (42 LCD_R3), R26.1, R28.1
/SRC_BCLK_F: M1.1 (73 HSPI_DIN2), U13.25 (BCKO)
/SRC_LRCK_F: M1.2 (74 HSPI_DIN3), U13.24 (LRCKO)
/TX_FB: M1.10 (25 LCD_HS), R16.2
/TX_PRE: M1.9 (28 LCD_B6), U9.1 (D)
/TX_REGEN: R9.1, R16.1, U2.1 (I1), U9.4 (Q), U11.2 (B)
/TX_SEL: U2.6 (S), U11.5 (Q)
/UART_RX_F: M1.23 (76 HSPI_DAT), R20.1
/UART_TX_F: M1.27 (56 I2S_BCLK), M2.32 (IO4), R18.1
/WAKE: U4.5 (Q), U6.2 (EN)
GND: C1.2, C2.2, C3.2, C4.2, C7.2, C8.2, C10.2, C11.2, C12.2, C13.2, C14.2, C15.2, C16.2, C17.2, C18.2, C19.2, C20.2, C23.2, C24.2, C26.2, C27.2, C28.2, C30.2, C31.2, C32.2, C33.2, C34.2, C35.2, C36.2, C37.2, C38.2, C39.2, C40.2, C43.2, C44.2, C45.2, C46.2, C47.2, C48.2, C49.2, C50.2, C51.2, C52.2, C53.2, C54.2, C55.2, C56.2, C58.2, C59.2, C60.2, C61.2, C62.2, C63.2, C64.2, C65.2, C66.2, C67.2, C68.2, C71.2, C72.1, C73.2, C75.2, C76.2, C77.2, C78.2, C79.2, C80.2, C81.2, C82.2, C83.2, C84.2, C85.2, D2.2 (A), D4.2 (A2), D5.2 (A2), D6.2 (A2), J1.0 (SHIELD), J1.2 (TXGND), J1.6 (RXGND), J2.7 (GND), J2.8 (GND), J3.5 (GND), J3.6 (GND), J4.2 (GND), J5.2 (GND), J6.1 (GND), J7.2 (Ext), J8.2 (Ext), J9.2 (Ext), M1.20 (GND), M1.22 (GND), M1.35 (GND), M2.14 (GND), M2.20 (GND), M2.26 (GND), R5.2, R7.2, R8.2, R9.2, R14.2, R17.2, R22.2, R27.2, R31.1, TP9.1, U1.3 (GND), U2.2 (GND), U3.1 (~OE), U3.3 (GND), U4.1 (~A), U4.4 (GND), U5.3 (GND), U5.4 (GND), U5.7 (PAD), U6.1 (GND), U6.9 (EP), U7.3 (GND), U8.2 (GND), U9.3 (GND), U10.2 (GND), U11.1 (~A), U11.4 (GND), U12.6 (DGND), U12.8 (XTI), U12.13 (PSCK0), U12.14 (PSCK1), U12.19 (RSV), U12.23 (AGND), U12.28 (CKSEL), U13.1 (LGRP), U13.8 (DGND), U13.9 (BYPAS), U13.11 (IFMT1), U13.12 (IFMT2), U13.16 (OWL1), U13.17 (OWL0), U13.18 (OFMT1), U13.20 (TDMI), U13.21 (DGND), U13.26 (MODE0), U13.27 (MODE1), U13.28 (MODE2), U14.2 (GND), U15.3 (CPGND), U15.9 (AGND), U15.10 (DEMP), U15.11 (FLT), U15.12 (SCK), U15.16 (FMT), U15.19 (DGND), U16.2 (GND), U18.4 (GND), X1.2 (GND)
unnamed: C27.1, R24.1
unnamed: C29.1, R26.2, R27.1
unnamed: C69.1, R32.2, R43.1
unnamed: C70.1, R33.2, R44.1
unnamed: C83.1, D1.2 (A), D2.1 (K), F1.2
unnamed: D1.1 (K), L2.1
unnamed: D3.1 (K), M1.21 (5V)
unnamed: C29.2, D4.1 (A1), J7.1 (In)
unnamed: C61.1, D5.1 (A1), J8.1 (In), R45.2
unnamed: C62.1, D6.1 (A1), J9.1 (In), R46.2
unnamed: J1.4 (RGAIN), R3.2, R42.2
unnamed: J1.8 (RXD), R1.1
unnamed: C10.1, C18.1, FB1.2, J1.5 (RXVCC)
unnamed: J1.1 (TXD), R2.2
unnamed: C19.1, C20.1, FB2.1, J1.3 (TXVCC), R3.1, R42.1
unnamed: J2.6 (BCLK), R34.2
unnamed: J2.3 (FS), R35.2
unnamed: J2.4 (MCLK), R19.2
unnamed: J2.1 (SD0), R36.2
unnamed: J2.2 (SD1), R37.2
unnamed: J2.5 (UART_TX), R18.2
unnamed: J3.4 (BCLK), R39.2
unnamed: J3.2 (DOUT), R41.2
unnamed: J3.3 (LRCK), R40.2
unnamed: J3.1 (MCLK), R38.2
unnamed: F1.1, J4.1 (VBAT)
unnamed: C30.1, FB3.1, J5.3 (VCC)
unnamed: J5.1 (VOUT), R25.1
unnamed: J6.3 (VIN), R28.2
unnamed: M2.35 (IO15), R20.2
unnamed: M2.25 (IO21), R21.2
unnamed: R1.2, R7.1, U1.2 (A)
unnamed: R53.1, U1.4 (Y)
unnamed: R2.1, U2.4 (Y)
unnamed: C9.2, U4.6 (CEXT)
unnamed: C9.1, R6.2, U4.7 (REXT/CEXT)
unnamed: C6.1, U6.7 (BOOT)
unnamed: R4.2, R5.1, U6.5 (FB)
unnamed: R31.2, U6.4 (RT/SYNC)
unnamed: C6.2, L1.1, U6.8 (SW)
unnamed: R10.1, R15.1, U7.4 (CLK+)
unnamed: C13.1, C14.1, U7.6 (VDD), U8.5 (OUT)
unnamed: R22.1, U10.5 (ILIM)
unnamed: C25.2, U11.6 (CEXT)
unnamed: C25.1, R23.2, U11.7 (REXT/CEXT)
unnamed: U12.11 (BCKO), U13.5 (BCKI)
unnamed: U12.12 (DOUT), U13.4 (SDIN)
unnamed: C28.1, R24.2, U12.22 (FILT)
unnamed: U12.10 (LRCKO), U13.6 (LRCKI)
unnamed: R25.2, U12.20 (RXIN)
unnamed: U13.14 (MUTE), U13.15 (RDY)
unnamed: U13.2 (RCKI), X1.3 (OUT)
unnamed: R29.1, U13.23 (SDOUT)
unnamed: C57.2, U15.4 (CAPM)
unnamed: C57.1, U15.2 (CAPP)
unnamed: C59.1, C60.1, U15.18 (LDOO)
unnamed: R32.1, U15.6 (OUTL)
unnamed: R33.1, U15.7 (OUTR)
unnamed: C58.1, U15.5 (VNEG)
unnamed: C72.2, R44.2, U17.3 (+A)
unnamed: C71.1, R43.2, U17.5 (+B)
unnamed: C70.2, R46.1, U17.1 (OA), U17.2 (-A)
unnamed: C69.2, R45.1, U17.6 (-B), U17.7 (OB)
unnamed: C74.1, U18.5 (C+)
unnamed: C74.2, U18.3 (C-)
VBAT_P: C1.1, C2.1, C4.1, C43.1, C44.1, C45.1, C46.1, C47.1, C82.1, L2.2, U5.1 (IN), U5.2 (EN), U6.3 (VIN)
VNEG_A: C77.1, C85.1, R48.2, U17.4 (V-)
VNEG_P: C75.1, R48.1, U18.1 (OUT)

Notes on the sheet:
1. ЖИВЛЕННЯ J4 акумулятор -> 3V3_AON (завжди) і 5V_SW (за WAKE) -> 5V_HOST (M2)
J4 Molex Micro-Fit 3.0 кутовий 43650-0200 на лівому краю під J1 (відповідна частина 43645-0200, контакти 43030), із защіпкою, 5 А. Захист: F1 2 А інерційний; D2 SMBJ36A перед D1: мовчить при 35 В (ISO 16750-2 B), імпульси ISO 7637-2 тисне до ~50 В.
3V3_AON (U5) завжди: FOT, U1, U2, U4, U11. На стоянці (кільце спить) разом до ~60 мкА: FOT у сні <= 25, логіка, LDO 2.7.
5V_SW (U6 LMR38020, 80 В, 400 кГц) вмикає WAKE: модуль FPGA і U14 (3V3_DA, блок 9). VOUT 5.31 В. C44/C45 + L2 22 мкГн: дзвін джгута і 400 кГц не в джгут.
5V_HOST (U10): живлення M2 (ESP32), межа ~1 А (R22 24k9): радіо модуля бере піки понад 0.5 А; 5 В з USB модуля назад у 5V_SW не проходять.
2. ПРОБУДЖЕННЯ (U4) І СТОРОЖ ОБХОДУ (U11)
U4: кожен фронт RX
перезапускає ~0.1 с
(R6 x C9). Кільце спить
-> WAKE = 0 -> U6 вимк.,
FPGA без живлення.
Полярність STATUS
знати не треба.
U11: TX_SEL = 1, лише
поки LOCK = 1 і фронти
TX_REGEN є (R23 x C25
~10 мкс; TX без фронтів
довше - не MOST).
TX став (такт, U9, FPGA)
-> TX_SEL = 0: обхід.
R8: FPGA не завантажена
-> LOCK = 0 -> обхід.
3. КІЛЬЦЕ J1 = вхід і вихід MOST (обидва волокна); ретрансляція, завжди живлено
волокно ВІД попереднього вузла -> RX
волокно ДО наступного вузла <- TX
S = TX_SEL = 0: FPGA вимкнена, без захоплення або TX став -> прямий прохід RX -> TX.
S = 1 (LOCK і фронти TX, U11): TX = перегенерований сигнал з FPGA. Мережа нас не бачить.
R3 || R42 = 2 x 27k = 13k5: RGAIN -> TXVCC (AN 5344: 13.5..33k).
FB1/FB2 + 100n + 10u: RX і TX окремо.
R7: RXD у 0, коли приймач спить.
4. РОЗВ'ЯЗКА FPGA, ТРИГЕР TX
U3, U9 від 3V3_SW: коли FPGA
вимкнена, вони (Ioff) не вантажать лінії.
U9: фронти TX на такті Si514 (RT_CLK).
Q -> U2 (TX_REGEN) і в FPGA (TX_FB).
5. FPGA Sipeed Tang Nano 20K
Контакти 1..20 / 21..40 згори вниз, від USB-C; назва = вивід GW2AR + що на ньому на платі (datasheet v1.3).
Кільце і Si514 - лише на виводах LCD (порожній роз'єм): LOCK на 31, S/PDIF на 42. HSPI, 54..56 (входи підсилювача модуля; PA_EN = 51 тримає його вимкненим), EDID 52/53: UART, MCLK, I2S, SD1, DIN2.
CLK_1024 (Si514) -> 77 (GCLKT_1). TX_FB -> 25 через IDES8 (1.26 нс); він займає пару, тому 26 не підключено.
D3: USB і 5V_SW разом не з'єднуються; U6 дає 5.3 В, на модулі ~5.0 В.

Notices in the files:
README.md:
Licence:
Copyright 2026 Oleg-mk.
- **Hardware, under CERN-OHL-S-2.0** ([LICENSE](LICENSE)):
- `listener_hw/` and `listener_hw2/`: the KiCad designs and the scripts that generate them,
the footprints and 3D models, the fabrication files, the tube's end caps, the pictures;
- the gateware in `listener_gw/rtl/` and `listener_gw/board/`;
- `kit/1_boards/` and `kit/2_flash/fpga/`.
- **Software, under GPL-3.0-or-later** ([COPYING](COPYING)): `listener_fw/` (the host's
firmware), `virtual_most_source/`, `tools/`, `listener_gw/sim/`, `kit/2_flash/esp32/`,
`kit/3_laptop/` and `check_all.py`.
